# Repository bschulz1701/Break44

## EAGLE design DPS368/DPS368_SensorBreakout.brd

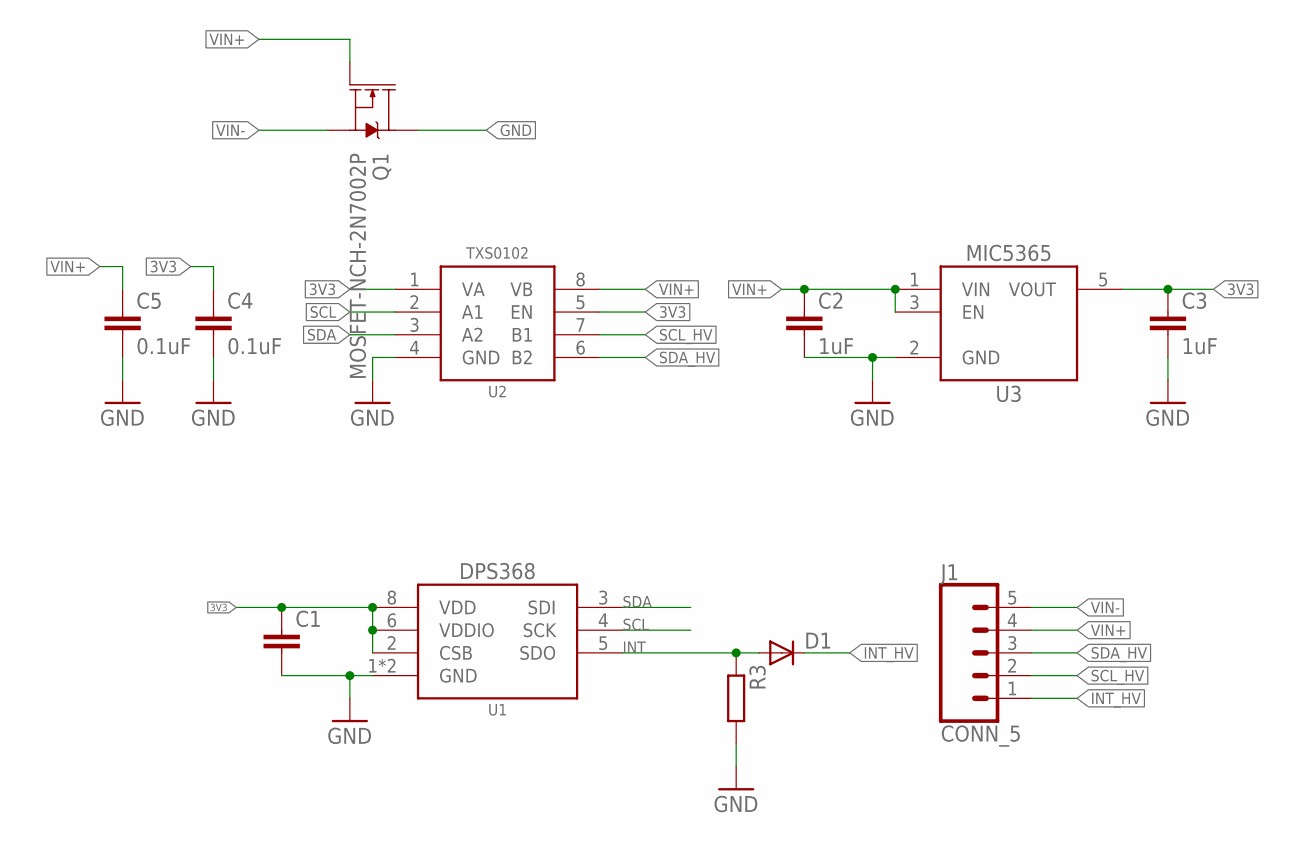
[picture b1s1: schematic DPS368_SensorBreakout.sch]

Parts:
C1: C-EU0.1UFC0603; C0603
C2, C3: 1uF; C0603
C4, C5: 0.1uF; C0603
D1: DIODESOD-323; SOD323-R
J1: CONN_5; 1X05
Q1: MOSFET-NCH-2N7002P; SOT23-3
R3: R-EU_100KR0603; R0603
U1: DPS368; PG-VLGA-8
U2: TXS0102DQM; DQM_R-PX2SON-N8
U3: MIC53653.3SC70; DCK_R-PDSO-G5

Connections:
3V3: C1.1, C3.1, C4.1, U1.2 (CSB), U1.6 (VDDIO), U1.8 (VDD), U2.1 (VA), U2.5 (EN), U3.5 (VOUT)
GND: C1.2, C2.2, C3.2, C4.2, C5.2, Q1.3 (D), R3.2, U1.1 (GND), U1.7 (GND), U2.4 (GND), U3.2 (GND)
INT: D1.A, R3.1, U1.5 (SDO)
INT_HV: D1.C, J1.1
SCL: U1.4 (SCK), U2.2 (A1)
SCL_HV: J1.2, U2.7 (B1)
SDA: U1.3 (SDI), U2.3 (A2)
SDA_HV: J1.3, U2.6 (B2)
VIN+: C2.1, C5.1, J1.4, Q1.1 (G), U2.8 (VB), U3.1 (VIN), U3.3 (EN)
VIN-: J1.5, Q1.2 (S)

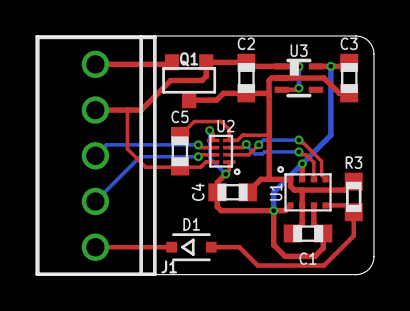
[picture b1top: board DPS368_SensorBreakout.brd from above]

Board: 2 copper layers, 18.8 x 13.3 mm, 12 parts (0 on the bottom side), 10 nets.

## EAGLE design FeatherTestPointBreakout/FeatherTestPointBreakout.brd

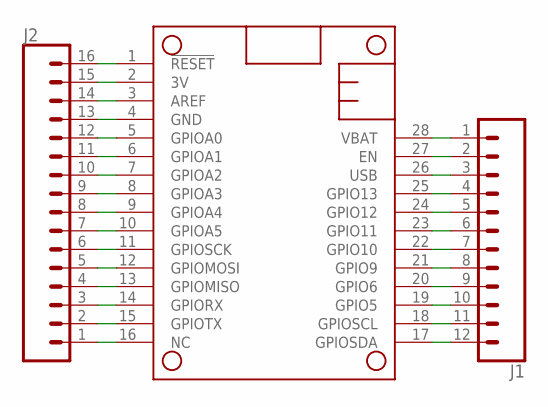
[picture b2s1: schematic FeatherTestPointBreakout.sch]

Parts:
J1: CONN_12; 1X12
J2: CONN_16; 1X16
MS1: FEATHERWINGLAYOUT; FEATHERWING_MIN

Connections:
3V: J2.15, MS1.2 (3V)
unnamed: J2.16, MS1.1 (!RESET)
unnamed: J2.14, MS1.3 (AREF)
unnamed: J2.13, MS1.4 (GND)
unnamed: J2.12, MS1.5 (GPIOA0)
unnamed: J2.11, MS1.6 (GPIOA1)
unnamed: J2.10, MS1.7 (GPIOA2)
unnamed: J2.9, MS1.8 (GPIOA3)
unnamed: J2.8, MS1.9 (GPIOA4)
unnamed: J2.7, MS1.10 (GPIOA5)
unnamed: J2.6, MS1.11 (GPIOSCK)
unnamed: J2.5, MS1.12 (GPIOMOSI)
unnamed: J2.4, MS1.13 (GPIOMISO)
unnamed: J2.3, MS1.14 (GPIORX)
unnamed: J2.2, MS1.15 (GPIOTX)
unnamed: J2.1, MS1.16 (NC)
unnamed: J1.12, MS1.17 (GPIOSDA)
unnamed: J1.11, MS1.18 (GPIOSCL)
unnamed: J1.10, MS1.19 (GPIO5)
unnamed: J1.9, MS1.20 (GPIO6)
unnamed: J1.8, MS1.21 (GPIO9)
unnamed: J1.7, MS1.22 (GPIO10)
unnamed: J1.6, MS1.23 (GPIO11)
unnamed: J1.5, MS1.24 (GPIO12)
unnamed: J1.4, MS1.25 (GPIO13)
unnamed: J1.2, MS1.27 (EN)
USB: J1.3, MS1.26 (USB)
VBAT: J1.1, MS1.28 (VBAT)

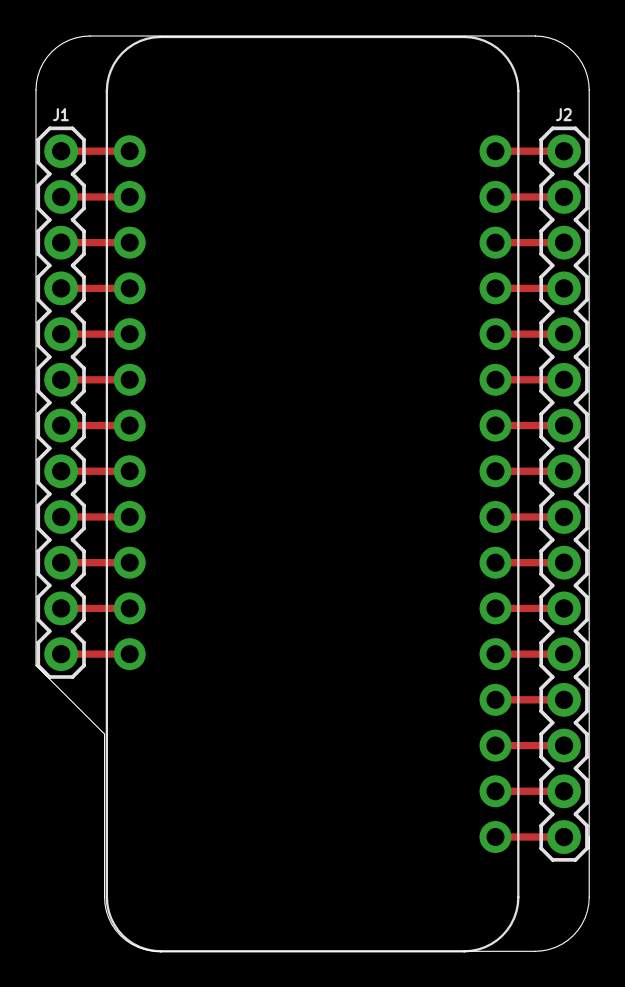
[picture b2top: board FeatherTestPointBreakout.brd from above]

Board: 2 copper layers, 30.7 x 50.9 mm, 3 parts (0 on the bottom side), 28 nets.

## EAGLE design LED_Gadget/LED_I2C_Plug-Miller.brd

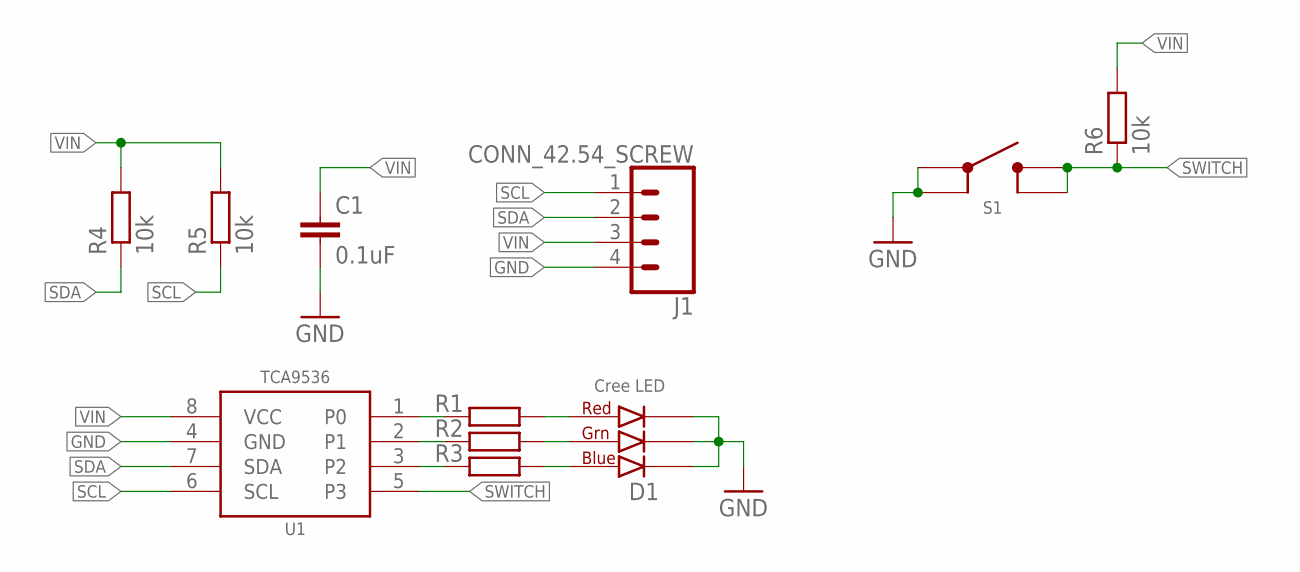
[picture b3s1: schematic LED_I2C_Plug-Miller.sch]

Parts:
C1: 0.1uF; C0603
D1: CLX6F-FKC
J1: CONN_42.54_SCREW; 1X04_SCREW
R1, R2, R3: R-EU_330R0603; R0603
R4, R5, R6: 10k; R0603
S1: BUTTON4.2X3.2; SWITCH_4.2X3.2
U1: PCA9536VSSOP; DGK_S-PDSO-G8

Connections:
GND: C1.2, D1.P$1 (4), D1.P$2 (5), D1.P$3 (6), J1.4, S1.1, S1.2, U1.4 (GND)
unnamed: D1.P$4 (1), R1.2
unnamed: D1.P$5 (2), R2.2
unnamed: D1.P$6 (3), R3.2
unnamed: R3.1, U1.3 (P2)
unnamed: R2.1, U1.2 (P1)
unnamed: R1.1, U1.1 (P0)
SCL: J1.1, R5.1, U1.6 (SCL)
SDA: J1.2, R4.1, U1.7 (SDA)
SWITCH: R6.1, S1.3 (4), S1.4 (3), U1.5 (P3)
VIN: C1.1, J1.3, R4.2, R5.2, R6.2, U1.8 (VCC)

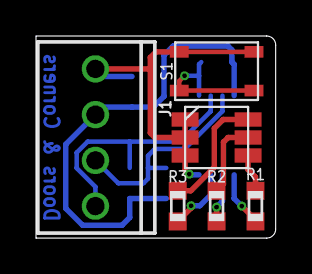
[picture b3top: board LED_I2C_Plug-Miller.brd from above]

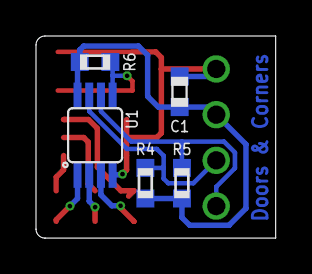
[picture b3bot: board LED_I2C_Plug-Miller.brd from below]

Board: 2 copper layers, 13.3 x 11.2 mm, 11 parts (5 on the bottom side), 11 nets.

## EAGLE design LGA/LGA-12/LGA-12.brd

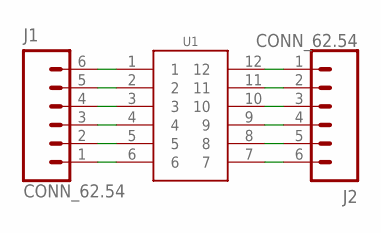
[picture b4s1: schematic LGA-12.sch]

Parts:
J1, J2: CONN_62.54; 1X06
U1: GEN_12LGA12_2X2; LGA-12_2X2

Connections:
unnamed: J1.6, U1.1
unnamed: J1.5, U1.2
unnamed: J1.4, U1.3
unnamed: J1.3, U1.4
unnamed: J1.2, U1.5
unnamed: J1.1, U1.6
unnamed: J2.1, U1.12
unnamed: J2.2, U1.11
unnamed: J2.3, U1.10
unnamed: J2.4, U1.9
unnamed: J2.5, U1.8
unnamed: J2.6, U1.7

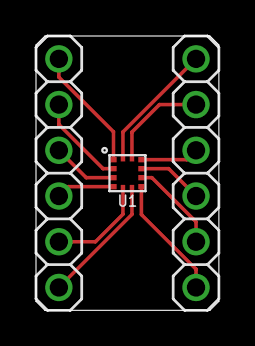
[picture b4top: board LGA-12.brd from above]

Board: 2 copper layers, 10.2 x 15.2 mm, 3 parts (0 on the bottom side), 12 nets.

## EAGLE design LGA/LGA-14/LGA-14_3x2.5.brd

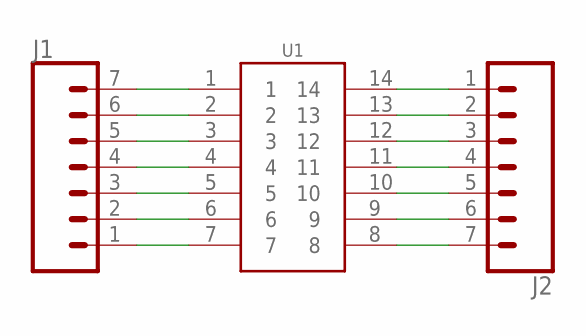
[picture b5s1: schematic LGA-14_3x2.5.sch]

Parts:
J1, J2: CONN_07; 1X07
U1: GEN_14LGA_3X2.5; PQFN50P250X300X97-14N

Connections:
unnamed: J1.1, U1.7
unnamed: J1.2, U1.6
unnamed: J1.3, U1.5
unnamed: J1.4, U1.4
unnamed: J1.5, U1.3
unnamed: J1.6, U1.2
unnamed: J1.7, U1.1
unnamed: J2.1, U1.14
unnamed: J2.2, U1.13
unnamed: J2.3, U1.12
unnamed: J2.4, U1.11
unnamed: J2.5, U1.10
unnamed: J2.6, U1.9
unnamed: J2.7, U1.8

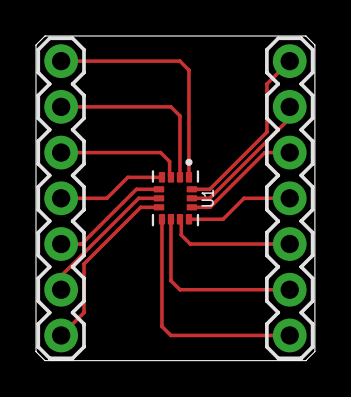
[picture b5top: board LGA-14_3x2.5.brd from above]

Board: 2 copper layers, 15.5 x 18.0 mm, 3 parts (0 on the bottom side), 14 nets.

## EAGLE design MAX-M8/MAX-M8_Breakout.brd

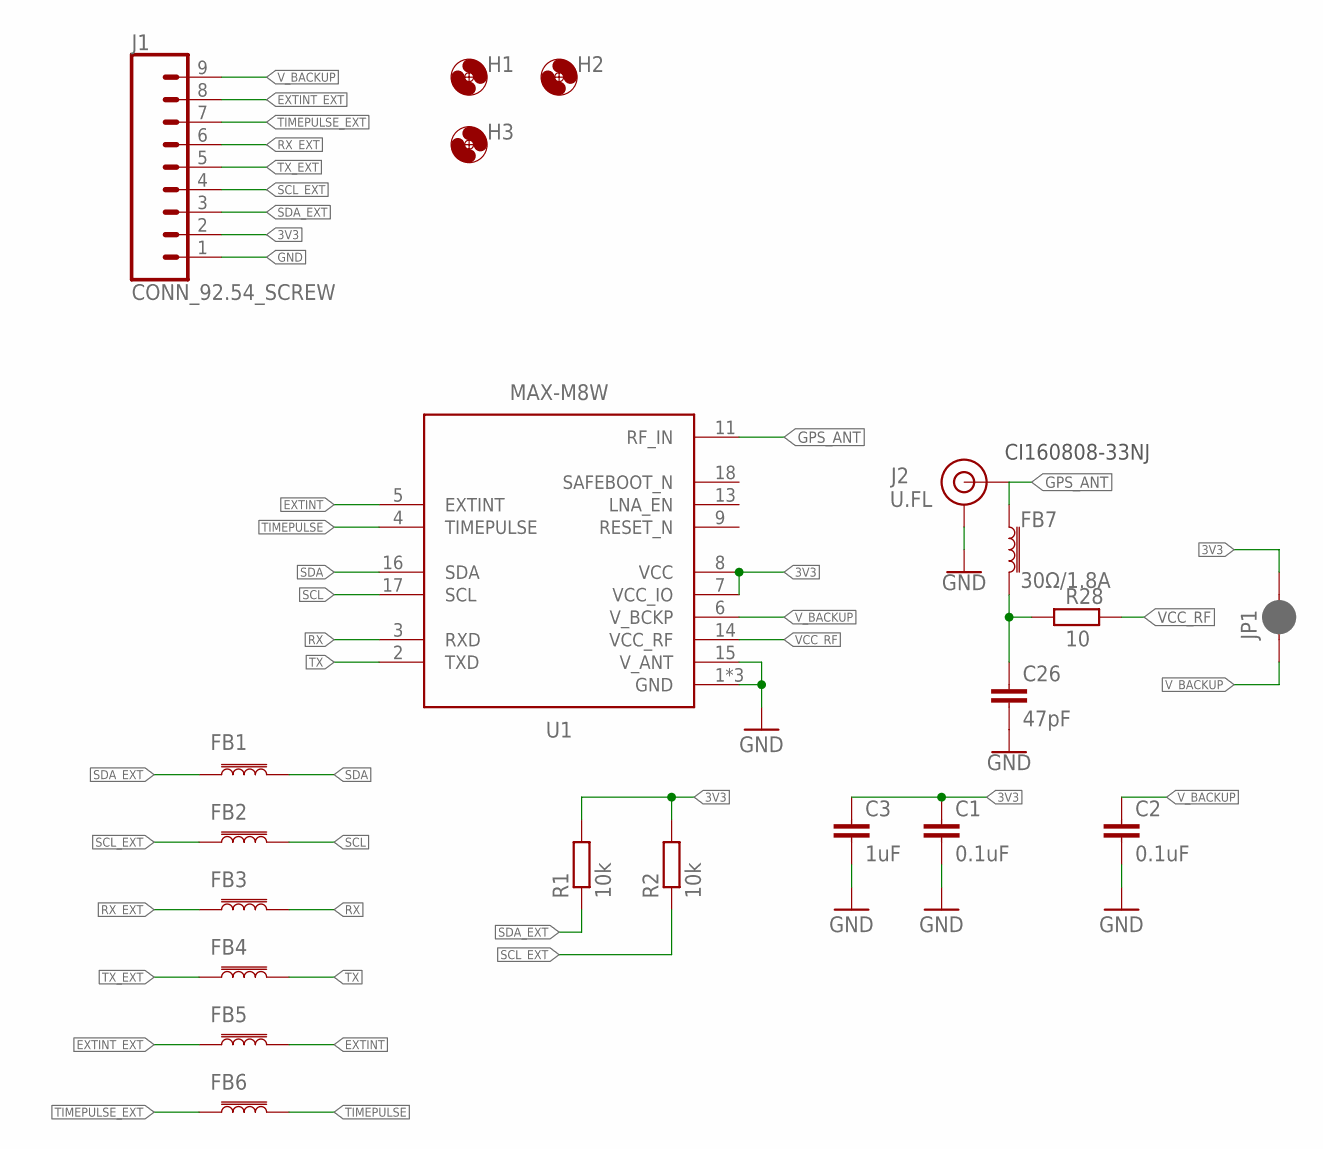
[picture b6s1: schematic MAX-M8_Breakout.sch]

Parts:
C1, C2: 0.1uF; C0603
C3: 1uF; C0603
C26: 47pF; C0402
FB1, FB2, FB3, FB4, FB5, FB6: FERRITE_BEAD1KS0402; R0402
FB7: 30Ω/1.8A; 0603; MPN MPZ1608D300BTA00; DIGIKEY 445-2986-1-ND
H1, H2, H3: MOUNTING_HOLE2_NP; 2_56
J1: CONN_92.54_SCREW; 1X09_SCREW
J2: U.FL; MPN 0734120110; DIGIKEY WM5587CT-ND
JP1: JUMPER-SMT_2_NC_PASTE_SILK; SMT-JUMPER_2_NC_PASTE_SILK
R1, R2: 10k; R0603
R28: 10; R0402
U1: MAX-M8W; MAX-M8

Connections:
3V3: C1.1, C3.1, J1.2, JP1.2, R1.2, R2.2, U1.7 (VCC_IO), U1.8 (VCC)
ANT_VCC: C26.1, FB7.2, R28.1
EXTINT: FB5.2, U1.5 (EXTINT)
EXTINT_EXT: FB5.1, J1.8
GND: C1.2, C2.2, C3.2, C26.2, J1.1, J2.1 (GND), J2.2 (GND), U1.1 (GND), U1.10 (GND), U1.12 (GND), U1.15 (V_ANT)
GPS_ANT: FB7.1, J2.FEED (SIGNAL), U1.11 (RF_IN)
RX: FB3.2, U1.3 (RXD)
RX_EXT: FB3.1, J1.6
SCL: FB2.2, U1.17 (SCL)
SCL_EXT: FB2.1, J1.4, R2.1
SDA: FB1.2, U1.16 (SDA)
SDA_EXT: FB1.1, J1.3, R1.1
TIMEPULSE: FB6.2, U1.4 (TIMEPULSE)
TIMEPULSE_EXT: FB6.1, J1.7
TX: FB4.2, U1.2 (TXD)
TX_EXT: FB4.1, J1.5
VCC_RF: R28.2, U1.14 (VCC_RF)
V_BACKUP: C2.1, J1.9, JP1.1, U1.6 (V_BCKP)

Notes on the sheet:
CI160808-33NJ

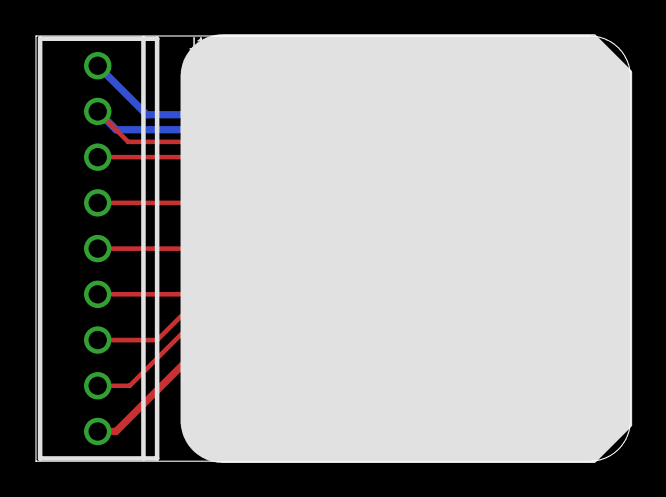
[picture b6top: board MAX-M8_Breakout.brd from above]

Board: 2 copper layers, 33.0 x 23.6 mm, 21 parts (0 on the bottom side), 18 nets.

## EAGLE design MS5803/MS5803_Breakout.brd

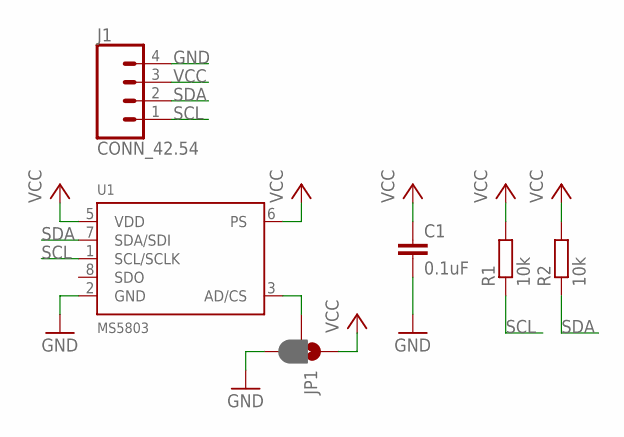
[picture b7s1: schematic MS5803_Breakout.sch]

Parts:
C1: 0.1uF; C0805
J1: CONN_42.54; 1X04
JP1: JUMPER-SMT_3_1-NC_PASTE_SILK; SMT-JUMPER_3_1-NC_PASTE_SILK
R1, R2: 10k; R0805
U1: MS5803

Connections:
GND: C1.2, J1.4, JP1.3, U1.2 (GND)
unnamed: JP1.2, U1.3 (AD/CS)
SCL: J1.1, R1.1, U1.1 (SCL/SCLK)
SDA: J1.2, R2.1, U1.7 (SDA/SDI)
VCC: C1.1, J1.3, JP1.1, R1.2, R2.2, U1.5 (VDD), U1.6 (PS)

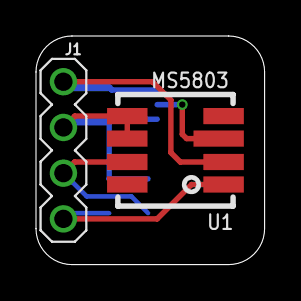
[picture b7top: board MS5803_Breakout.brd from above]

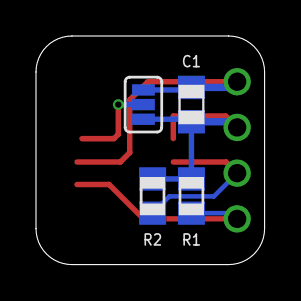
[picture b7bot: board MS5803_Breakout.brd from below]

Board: 2 copper layers, 12.7 x 12.7 mm, 6 parts (4 on the bottom side), 5 nets.

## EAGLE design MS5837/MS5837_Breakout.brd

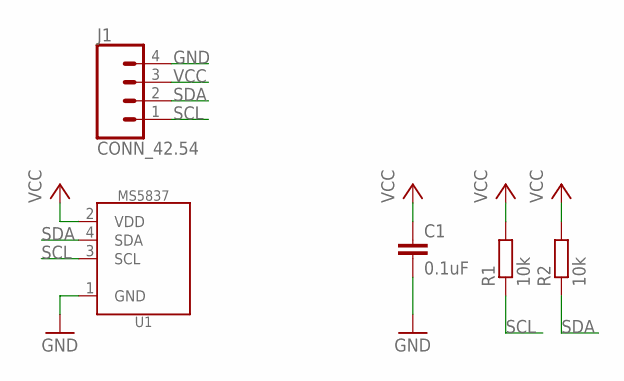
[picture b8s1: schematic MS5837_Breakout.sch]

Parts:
C1: 0.1uF; C0805
J1: CONN_42.54; 1X04
R1, R2: 10k; R0805
U1: MS5837

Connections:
GND: C1.2, J1.4, U1.1 (GND)
SCL: J1.1, R1.1, U1.3 (SCL)
SDA: J1.2, R2.1, U1.4 (SDA)
VCC: C1.1, J1.3, R1.2, R2.2, U1.2 (VDD)

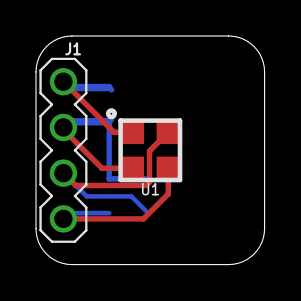
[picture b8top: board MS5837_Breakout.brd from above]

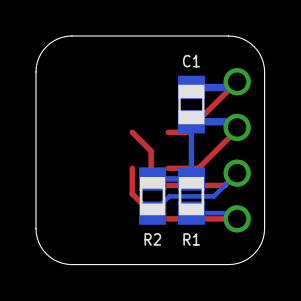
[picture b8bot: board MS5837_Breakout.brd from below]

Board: 2 copper layers, 12.7 x 12.7 mm, 5 parts (3 on the bottom side), 4 nets.

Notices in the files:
parts and their libraries:
SparkFun-Connectors: Licensing: Creative Commons ShareAlike 4.0 International - https://creativecommons.org/licenses/by-sa/4.0
